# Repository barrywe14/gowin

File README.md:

# Gowin Project
Dokumentasi Elektronik Produk pertanian Gowin (Dropper Biji Jagung). 

# Rangkaian Elektronik Gowin
Secara general sistem elektrik Gowin

Dibawah ini adalah rangkaian di dalam kotak elektronik 

Rangkaian Elektronik dalam bentuk PDF bisa [klik disini](/circuit/GoWinElectricalv2/GowinController-Controller.pdf)

## Program Arduino
Program Alat bisa klik [disini](/circuit/GoWinElectricalv1/program/GowinScript/GowinScript.ino)
Kemudian program untuk test hardware bisa klik [disini](/circuit/GoWinElectricalv1/program/GowinTestScript/GowinTestScript.ino)
# Foto Dokumentasi
Kontrol, Kotak Elektronik, dan Instrument <br>

<br>
Dropper dan encoder 
<br>

<br>
Konektor kabel Dropper biji 
<br>

# Cara Pemakaian
1. Putar tombol switch disebelah kotak elektronik hitam. Pastikan indikator tegangan menyala !

2. Kemudian perhatikan tampilan pada lcd, dan tunggu muncul tulisan "Gowin" maka alat mulai beroperasi. Dan ketika ada tulisan "Jarak" dan "Drop" maka peralatan telah berjalan.

3. Untuk melakukan reset, maka tekan tombol "reset" pada display.

4. Untuk melakukan pengaturan, tekan tombol "Atur". Untuk mengubah parameter kalibrasi "Tick/Biji" bisa tekan tombol  ( up ) atau tombol ( down ). Satuan yang digunakan merupakan centimeter. Dan untuk mengubah parameter yang ingin diatur, tekan lagi tombol "Atur".

5. Untuk kembali beroperasi, tekan tombol ( u) dan tombol ( down ) bersamaan
## Perhatian
- Charge baterai ketika menunjukan 8.1 V, dan jangan sampai melebihi 12V. Indikator terlihat pada kotak elektronik.
# Aplikasi Pendukung

 1. [KiCad](http://kicad-pcb.org/) sebagai pembuat skematik
 2. [draw.io](https://www.draw.io/) sebagai aplikai pembuat diagram
 3. [Arduino IDE](https://www.arduino.cc/)  sebagai IDE untuk memprogram Arduino UNO

# Partner Terlibat
UASC Manufacturing

<!--stackedit_data:
eyJoaXN0b3J5IjpbLTEzMDU3OTI3MTMsMTM5MDQ3NDI5NSwtOT
Y0OTIyNzIyLDE1NTUzMjI2NjksODQ4MjQyMDcwLDEyMTYxMDU5
NjgsLTE2MjAwMDk1MjcsLTc1NTIxMDQxOSwxNzA3NzkyODIyLC
0zNDkxMjc4MiwyMzMzOTI4MjUsMTk4Nzk2NDMzNiwxMzcwNDA3
MDMsMTM3MDQwNzAzXX0=
-->

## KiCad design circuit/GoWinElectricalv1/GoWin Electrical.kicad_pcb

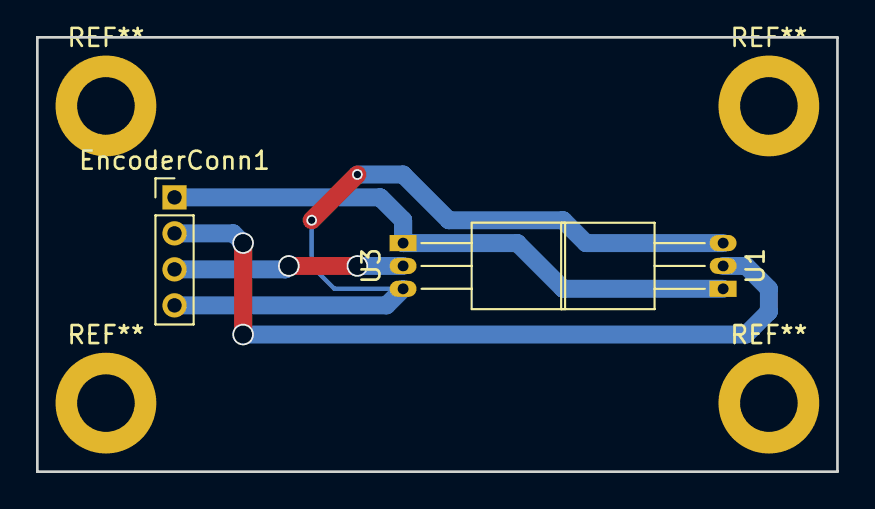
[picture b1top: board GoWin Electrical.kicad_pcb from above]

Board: 2 copper layers, 44.5 x 24.1 mm, 3 parts (0 on the bottom side), 4 nets.

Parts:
EncoderConn1: Conn_01x04_Female; Pin_Header_Straight_1x04_Pitch2.00mm
U1, U3: A1301KLHLT-T; TO-92_Horizontal2_Inline_Narrow_Oval

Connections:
+5V: EncoderConn1.1, U1.1, U3.1
/Encoder Roda/EncoderDir: EncoderConn1.3, U3.2
Encoder: EncoderConn1.2, U1.2
GND: EncoderConn1.4, U1.3, U3.3

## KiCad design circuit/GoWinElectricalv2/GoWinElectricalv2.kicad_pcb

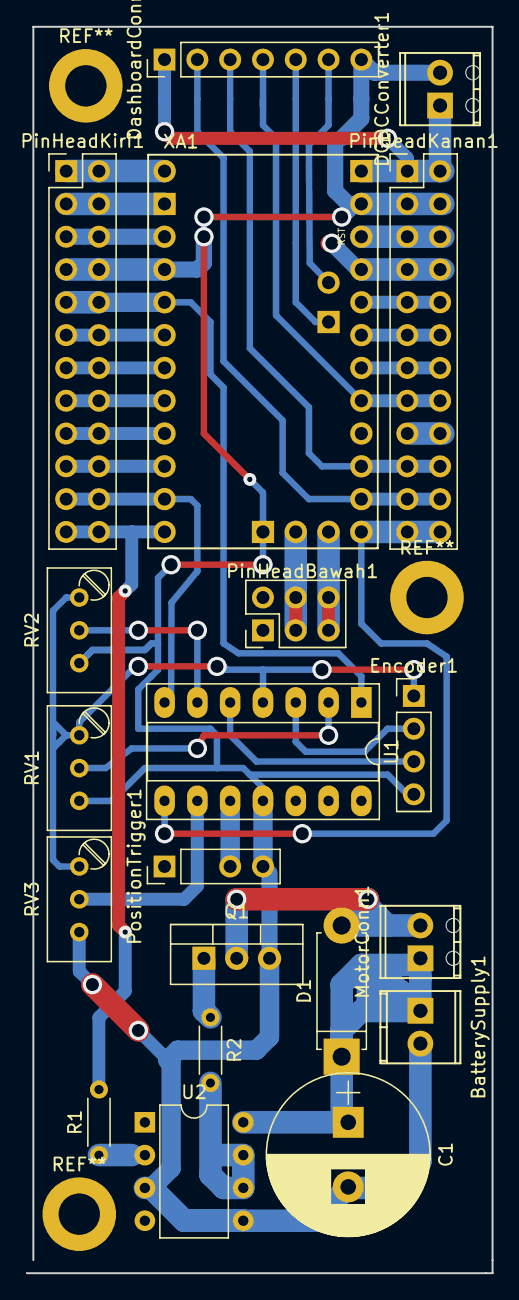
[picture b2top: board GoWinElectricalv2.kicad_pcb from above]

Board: 4 copper layers, 36.1 x 96.5 mm, 20 parts (0 on the bottom side), 37 nets.

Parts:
BatterySupply1: Conn_1x2; TerminalBlock_Phoenix_MPT-2.54mm_2pol
C1: CP; CP_Radial_D12.5mm_P5.00mm
D1: D; D_5W_P10.16mm_Horizontal
DCDCConverter1: Conn_1x2; TerminalBlock_Phoenix_MPT-2.54mm_2pol
DashboardConn1: XH2.54_7p; Pin_Header_Straight_1x07_Pitch2.54mm
Encoder1: XH2.54_4p; Pin_Header_Straight_1x04_Pitch2.54mm
MotorConn1: Conn_1x2; TerminalBlock_Phoenix_MPT-2.54mm_2pol
PinHeadBawah1: Conn_02x03_Odd_Even; Pin_Header_Straight_2x03_Pitch2.54mm
PinHeadKanan1: Conn_02x12_Odd_Even; Pin_Header_Straight_2x12_Pitch2.54mm
PinHeadKiri1: Conn_02x12_Odd_Even; Pin_Header_Straight_2x12_Pitch2.54mm
PositionTrigger1: XH2.54_4p; Pin_Header_Straight_1x04_Pitch2.54mm
Q1: IRF3205; TO-220-3_Vertical
R1, R2: R; R_Axial_DIN0204_L3.6mm_D1.6mm_P5.08mm_Horizontal
RV1, RV2, RV3: POT_TRIM; Potentiometer_Trimmer_Bourns_3296W
U1: LM324; DIP-14_W7.62mm_Socket_LongPads
U2: HCPL3120; DIP-8_W7.62mm
XA1: Arduino_Mini_01_Socket; Arduino_Mini_Socket

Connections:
+5V: Encoder1.1, PinHeadKanan1.7, PinHeadKanan1.8, RV1.1, RV2.1, RV3.1, U1.4, XA1.5V1
+BATT: BatterySupply1.1, C1.1, D1.1, MotorConn1.1, U2.8
+VDC: DCDCConverter1.1, DashboardConn1.1, PinHeadKanan1.1, PinHeadKanan1.2, XA1.VIN
/Controller/A1: PinHeadKanan1.13, PinHeadKanan1.14, XA1.A1
/Controller/A2: PinHeadKanan1.11, PinHeadKanan1.12, XA1.A2
/Controller/A3: PinHeadKanan1.9, PinHeadKanan1.10, XA1.A3
/Controller/A6: PinHeadBawah1.3, PinHeadBawah1.4, XA1.A6
/Controller/A7: PinHeadBawah1.5, PinHeadBawah1.6, XA1.A7
/Controller/Button_User_1_IN: DashboardConn1.2, PinHeadKanan1.21, PinHeadKanan1.22, XA1.D11
/Controller/Button_User_2_IN: DashboardConn1.3, PinHeadKanan1.19, PinHeadKanan1.20, XA1.D12
/Controller/Button_User_3_IN: DashboardConn1.4, PinHeadKanan1.15, PinHeadKanan1.16, XA1.A0, XA1.D13
/Controller/D3: PinHeadKiri1.11, PinHeadKiri1.12, XA1.D3
/Controller/D4: PinHeadKiri1.13, PinHeadKiri1.14, XA1.D4
/Controller/D5: PinHeadKiri1.15, PinHeadKiri1.16, XA1.D5
/Controller/D6: PinHeadKiri1.17, PinHeadKiri1.18, XA1.D6
/Controller/D7: PinHeadKiri1.19, PinHeadKiri1.20, XA1.D7
/Controller/ENCODER_IN_Dir: PinHeadKiri1.21, PinHeadKiri1.22, U1.7, XA1.D8
/Controller/ENCODER_IN_Tick: PinHeadKiri1.9, PinHeadKiri1.10, U1.1, XA1.D2
/Controller/Encoder_Dir: Encoder1.3, U1.5
/Controller/Encoder_Tick: Encoder1.2, U1.3
/Controller/LCD_SCL: DashboardConn1.6, XA1.A5
/Controller/LCD_SDA: DashboardConn1.5, XA1.A4
/Controller/MOTOR-: D1.2, MotorConn1.2, Q1.2
/Controller/MotorPWM_OUT: PinHeadKiri1.23, PinHeadKiri1.24, R1.2, XA1.D9
/Controller/PositionTrigger: PositionTrigger1.3, U1.10
/Controller/PositionTrigger_IN: PinHeadKanan1.23, PinHeadKanan1.24, U1.8, XA1.D10
/Controller/RXI: PinHeadKiri1.3, PinHeadKiri1.4, XA1.D1
/Controller/Reset: PinHeadKanan1.5, PinHeadKanan1.6, PinHeadKiri1.5, PinHeadKiri1.6, XA1.RST2
/Controller/TXO: PinHeadKiri1.1, PinHeadKiri1.2, XA1.D0
GND: BatterySupply1.2, C1.2, DCDCConverter1.2, DashboardConn1.7, Encoder1.4, PinHeadKanan1.3, PinHeadKanan1.4, PinHeadKiri1.7, PinHeadKiri1.8, PositionTrigger1.4, Q1.3, RV1.3, RV2.3, RV3.3, U1.11, U2.3, U2.5, XA1.GND2, XA1.GND4, XA1.L0
unnamed: PinHeadKanan1.17, PinHeadKanan1.18
unnamed: Q1.1, R2.1
unnamed: R1.1, U2.2
unnamed: R2.2, U2.6, U2.7
unnamed: RV1.2, U1.2
unnamed: RV2.2, U1.6
unnamed: RV3.2, U1.9

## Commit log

2019-10-04 Update Nota dan desain 3d
2019-11-07 Update dokumentasi 07112019
2019-11-10 Update 11_11_2019
2019-11-11 Edit issue
2019-11-11 README.md updated from https://stackedit.io/
